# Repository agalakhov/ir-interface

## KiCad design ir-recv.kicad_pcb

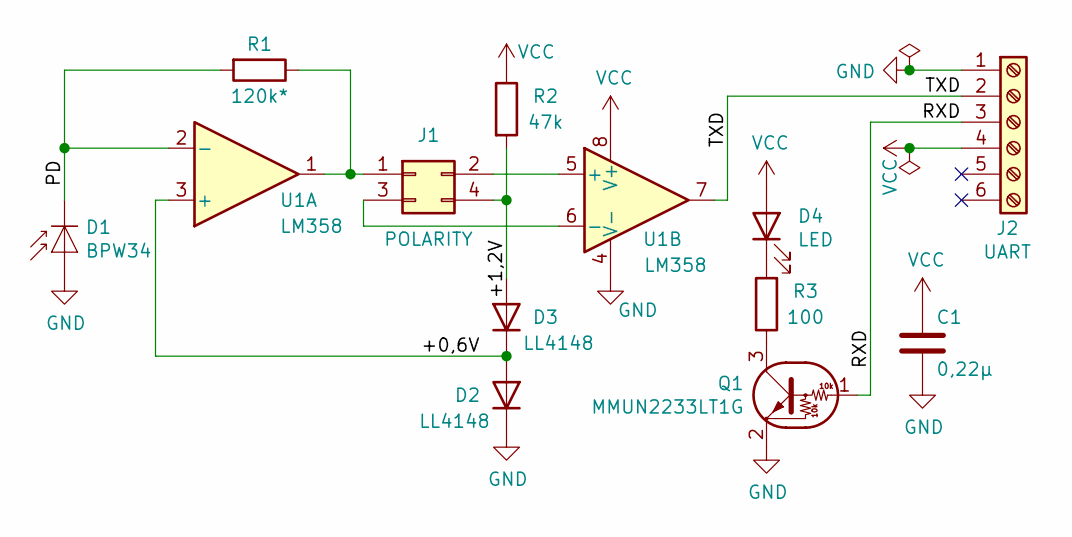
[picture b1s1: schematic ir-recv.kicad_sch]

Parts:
C1: 0,22µ; C_0805_2012Metric_Pad1.15x1.40mm_HandSolder
D1: BPW34; Osram_DIL2_4.3x4.65mm_P5.08mm
D2, D3: LL4148; D_MiniMELF
D4: LED; LED_D5.0mm
J1: POLARITY; PinHeader_2x02_P2.54mm_Vertical
J2: UART; TerminalBlock_Phoenix_MPT-0,5-6-2.54_1x06_P2.54mm_Horizontal
Q1: MMUN2233LT1G; SOT-23_Handsoldering
R1: 120k*; R_0805_2012Metric_Pad1.15x1.40mm_HandSolder
R2: 47k; R_0805_2012Metric_Pad1.15x1.40mm_HandSolder
R3: 100; R_0805_2012Metric_Pad1.15x1.40mm_HandSolder
U1: LM358; SOIC-8_3.9x4.9mm_P1.27mm

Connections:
/+0,6V: D2.2 (A), D3.1 (K), U1.3 (+)
/+1,2V: D3.2 (A), J1.4, R2.2
/PD: D1.1 (K), R1.2, U1.2 (-)
/RXD: J2.3, Q1.1 (B)
/TXD: J2.2, U1.7
GND: C1.2, D1.2 (A), D2.1 (K), J2.1, Q1.2 (E), U1.4 (V-)
unnamed: D4.1 (K), R3.2
unnamed: J1.2, U1.5 (+)
unnamed: J1.3, U1.6 (-)
unnamed: J1.1, R1.1, U1.1
unnamed: Q1.3 (C), R3.1
VCC: C1.1, D4.2 (A), J2.4, R2.1, U1.8 (V+)

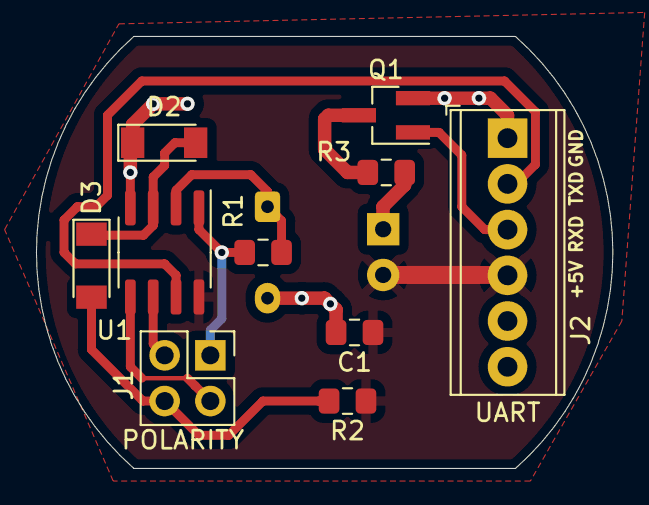
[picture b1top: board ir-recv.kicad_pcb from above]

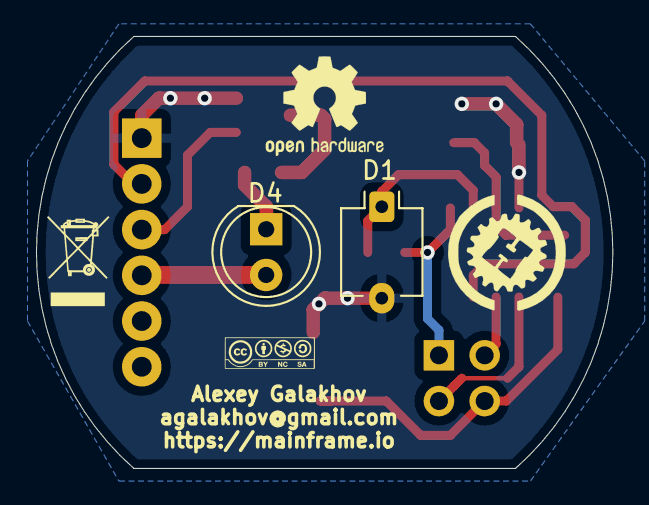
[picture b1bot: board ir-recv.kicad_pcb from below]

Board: 2 copper layers, 32.0 x 24.0 mm, 12 parts (2 on the bottom side), 12 nets.

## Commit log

2021-04-03 Set theme jekyll-theme-hacker
2021-12-08 Add BOM and manual
2021-12-08 Formatting
2021-12-08 Add board
